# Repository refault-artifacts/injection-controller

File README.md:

# DDR5 Injection controller
Hardware design files and firmware for the injection controller PCB that
controls the DDR5 interposer PCB by using a Teensy 4.1 microcontroller. This is
a 2-layer PCB.

## Design
The schematic and PCB was designed in KiCAD. Open `hardware/injection-controller.kicad_pro` in KiCAD 8 or later to view the design files.
From there, you should be able to select the schematic and PCB layout.

For convenience, you can also find a PDF version of the schematic in `docs/schematic.pdf`. A bill of materials (BOM) is also provided in `docs`.

### !!! Important !!!
This injection controller was designed for a previous version
of interposer with a different pinout on the flat-flex connector.
This works fine as long as the software is modified accordingly,
but it means that the labels of J2 in the schematic of the injection
controller (e.g., `CA4_LOW`) are not accurate anymore.
Instead, match the pin number of J2 to the appropriate function
of the interposer that you use.
The latest fault injection interposer also requires 3.3 V instead
of 1.1V. Hence, the voltage regulator U2 should be replaced
with a 3.3V type.
To be able to power-cycle the experiment machine, we manually
added a mechanical relay with a driving transistor and flyback diode
to the PCB. Those components are not documented here.

## Features

  - **Ethernet**: RJ45 Jack connected to the Ethernet header pins of the Teensy.
 - **Pluggable Teensy**: The Teensy microcontroller board is meant to be
 attached to the PCB by using headers, allowing for easy replacement and
 swapping of microcontroller.
 - **Status LED**: One power LED and one user controllable LED on the board.
- **Flat flex connector**: By using a suitable flat flex cable, the controller
 can be easily connected to the DDR5 fault injector interposer.

## Manufacturing
The PCBs were manufactured by JLCPCB and were assembled by hand.
It is reasonable to also order a SMT stencil so soldering is easier.
The Gerber files needed for manufacturing are located at hardware/output.

### Manufactoring options
| Option  | Value   |
|---------|---------|
| Layers  |   2     |
| Dimension | 60.96 mm* 40 mm |
| Product Type | Industrial/Consumer electronics |
| Different Design | 1|
| Delivery Format | Single PCB|
| PCB Thickness | 1.6|
| Impedance Control | no|
| Layer Sequence ||
| PCB Color | Green|
| Silkscreen | White|
| Via Covering | Tented|
| Surface Finish | LeadFree HASL|
| Deburring/Edge rounding | No|
| Outer Copper Weight | 1|
| Gold Fingers | No|
| Flying Probe Test | Fully Test|
| Castellated Holes | no|
| Remove Order Number | No|
| 4-Wire Kelvin Test | No|
| Material Type | FR4-Standard TG 135-140|
| Paper between PCBs | No|
| Appearance Quality | IPC Class 2 Standard|
| Confirm Production file | No|
| Silkscreen Technology | Ink-jet/Screen Printing Silkscreen|
| Package Box | With JLCPCB logo |

## Assembly
Assembly can be done manually using a stencil (ordered with the PCB),
some solder paste and a hot air gun.
### Bill of Materials (BOM)
See docs/bom

## License
Some parts of the PCB may be subject to copyright of third parties 
(e.g. 3D models provided by manufacturer).
Otherwise, the design is released under MIT License.

The KiCad symbol and footprint libraries for the Teensy microcontroller 
are taken from [here](https://github.com/XenGi/teensy_library) 
and [here](https://github.com/XenGi/teensy.pretty), respectively (MIT License).

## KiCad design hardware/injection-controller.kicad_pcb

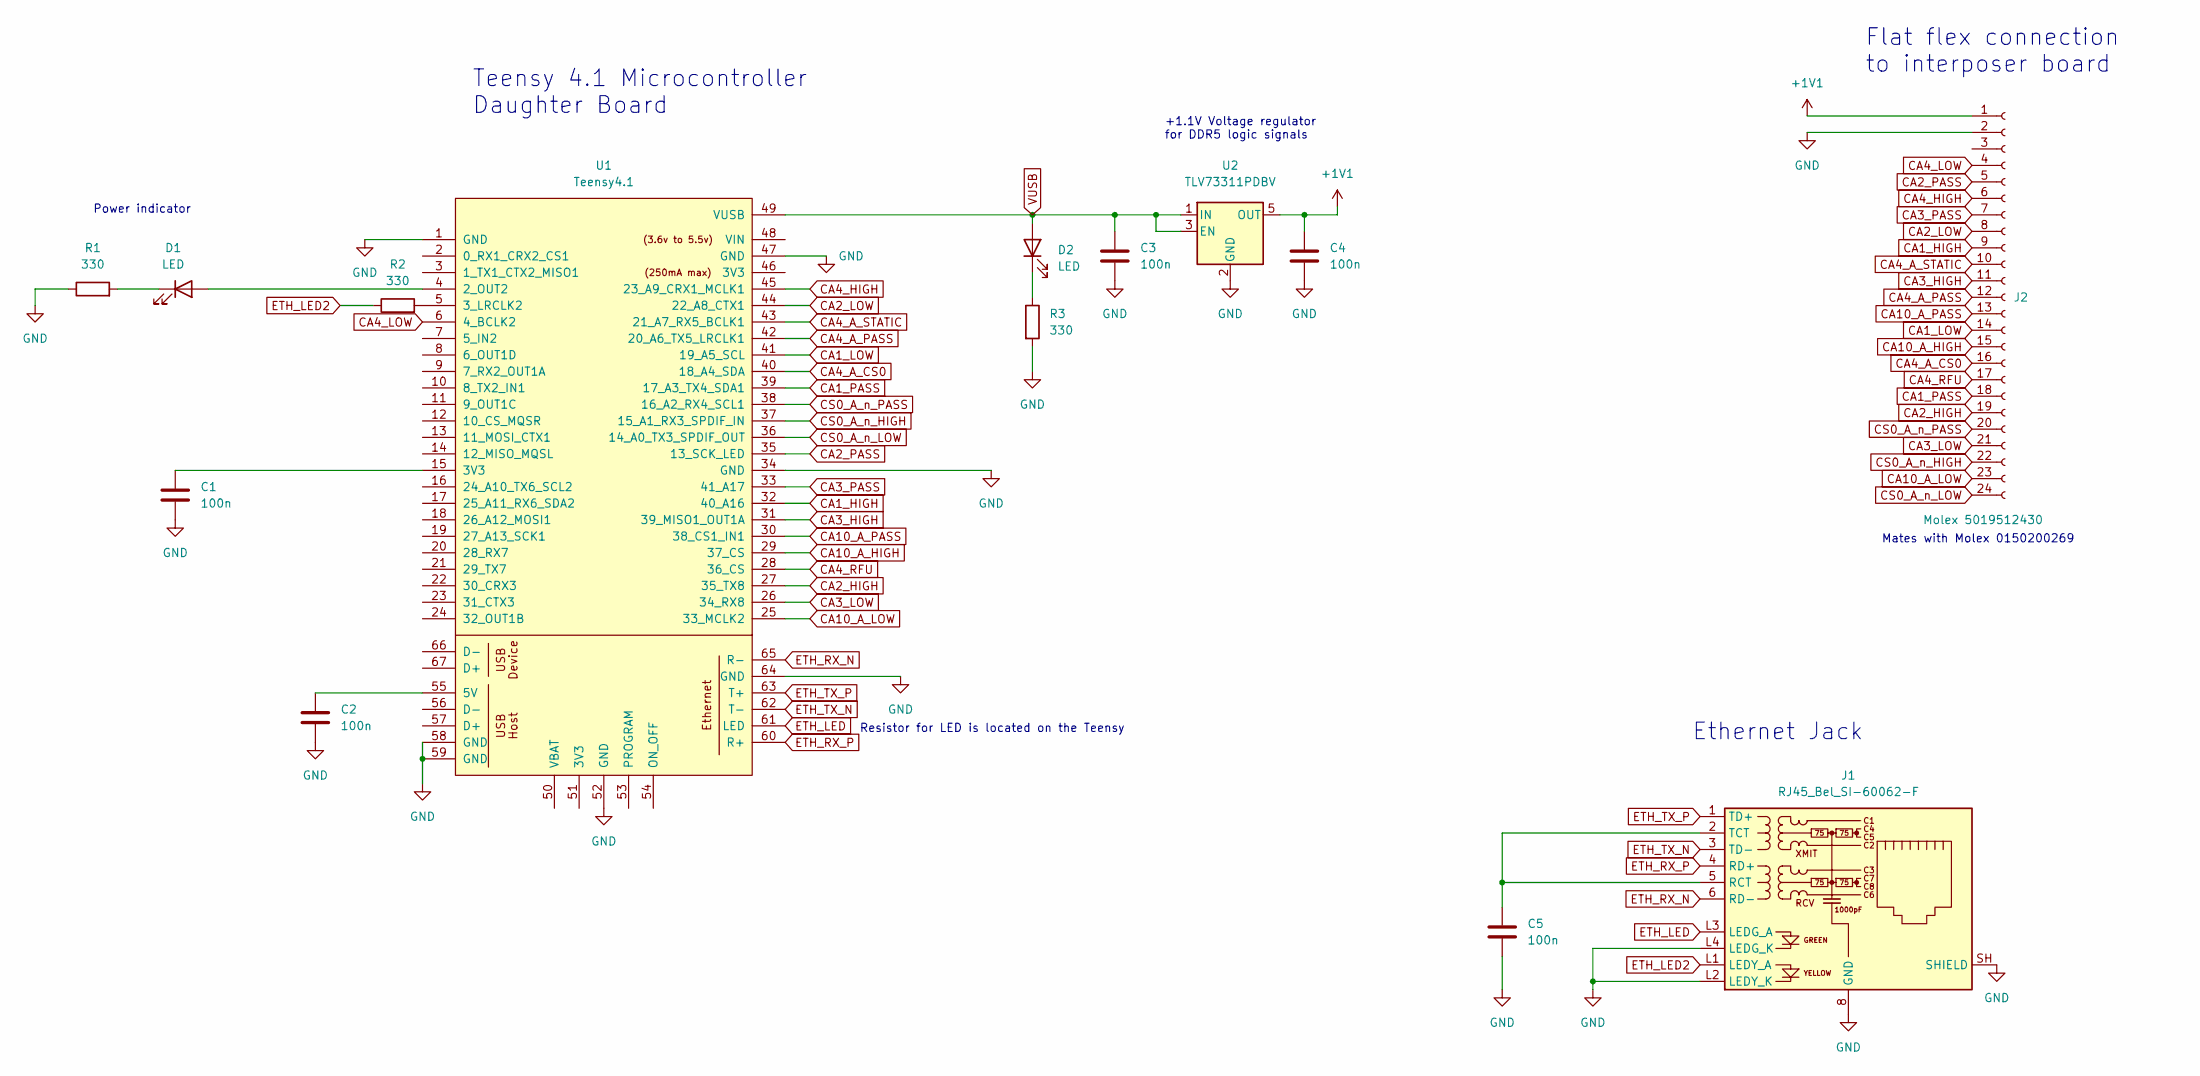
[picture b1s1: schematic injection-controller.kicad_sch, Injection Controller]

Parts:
C1, C2, C3, C4, C5: 100n; C_0603_1608Metric
D1, D2: LED; LED_0805_2012Metric
J1: RJ45_Bel_SI-60062-F; 480251090
J2: Molex 5019512430; 5019512430
R1, R2, R3: 330; R_0603_1608Metric
U1: Teensy4.1; Teensy41
U2: TLV73311PDBV; SOT-23-5

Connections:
+1V1: C4.1, J2.1, U2.5 (OUT)
CA1_HIGH: J2.9, U1.32 (40_A16)
CA1_LOW: J2.14, U1.41 (19_A5_SCL)
CA1_PASS: J2.18, U1.39 (17_A3_TX4_SDA1)
CA2_HIGH: J2.19, U1.27 (35_TX8)
CA2_LOW: J2.8, U1.44 (22_A8_CTX1)
CA2_PASS: J2.5, U1.35 (13_SCK_LED)
CA3_HIGH: J2.11, U1.31 (39_MISO1_OUT1A)
CA3_LOW: J2.21, U1.26 (34_RX8)
CA3_PASS: J2.7, U1.33 (41_A17)
CA4_A_CS0: J2.16, U1.40 (18_A4_SDA)
CA4_A_PASS: J2.12, U1.42 (20_A6_TX5_LRCLK1)
CA4_A_STATIC: J2.10, U1.43 (21_A7_RX5_BCLK1)
CA4_HIGH: J2.6, U1.45 (23_A9_CRX1_MCLK1)
CA4_LOW: J2.4, U1.6 (4_BCLK2)
CA4_RFU: J2.17, U1.28 (36_CS)
CA10_A_HIGH: J2.15, U1.29 (37_CS)
CA10_A_LOW: J2.23, U1.25 (33_MCLK2)
CA10_A_PASS: J2.13, U1.30 (38_CS1_IN1)
CS0_A_n_HIGH: J2.22, U1.37 (15_A1_RX3_SPDIF_IN)
CS0_A_n_LOW: J2.24, U1.36 (14_A0_TX3_SPDIF_OUT)
CS0_A_n_PASS: J2.20, U1.38 (16_A2_RX4_SCL1)
ETH_LED: J1.L3 (LEDG_A), U1.61 (LED)
ETH_LED2: J1.L1 (LEDY_A), R2.1
ETH_RX_N: J1.6 (RD-), U1.65 (R-)
ETH_RX_P: J1.4 (RD+), U1.60 (R+)
ETH_TX_N: J1.3 (TD-), U1.62 (T-)
ETH_TX_P: J1.1 (TD+), U1.63 (T+)
GND: C1.2, C2.2, C3.2, C4.2, C5.2, J1.8 (GND), J1.L2 (LEDY_K), J1.L4 (LEDG_K), J1.SH (SHIELD), J2.2, R1.1, R3.2, U1.1 (GND), U1.34 (GND), U1.47 (GND), U1.52 (GND), U1.58 (GND), U1.59 (GND), U1.64 (GND), U2.2 (GND)
unnamed: C1.1, U1.15 (3V3)
unnamed: C2.1, U1.55 (5V)
unnamed: C5.1, J1.2 (TCT), J1.5 (RCT)
unnamed: D1.1 (K), R1.2
unnamed: D1.2 (A), U1.4 (2_OUT2)
unnamed: D2.1 (K), R3.1
unnamed: R2.2, U1.5 (3_LRCLK2)
VUSB: C3.1, D2.2 (A), U1.49 (VUSB), U2.1 (IN), U2.3 (EN)

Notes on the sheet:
Mates with Molex 0150200269
+1.1V Voltage regulator for DDR5 logic signals
Flat flex connection to interposer board
Power indicator
Resistor for LED is located on the Teensy
Ethernet Jack
Teensy 4.1 Microcontroller Daughter Board

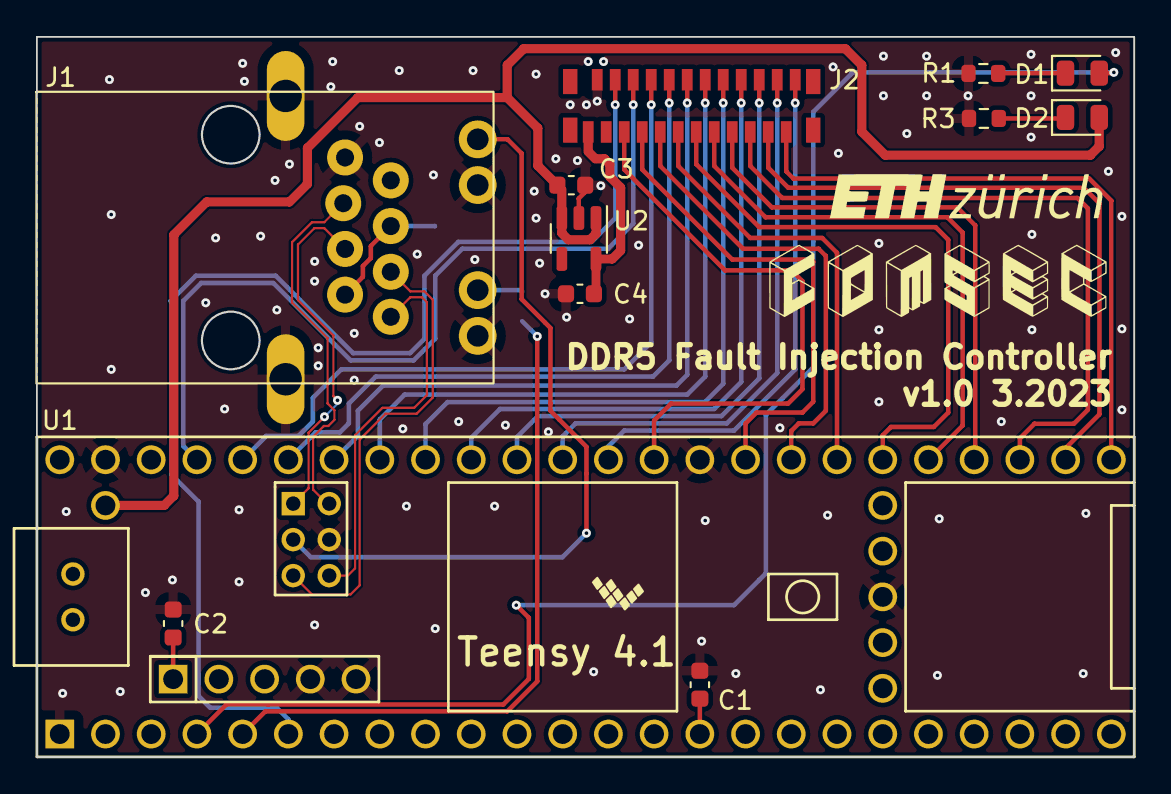
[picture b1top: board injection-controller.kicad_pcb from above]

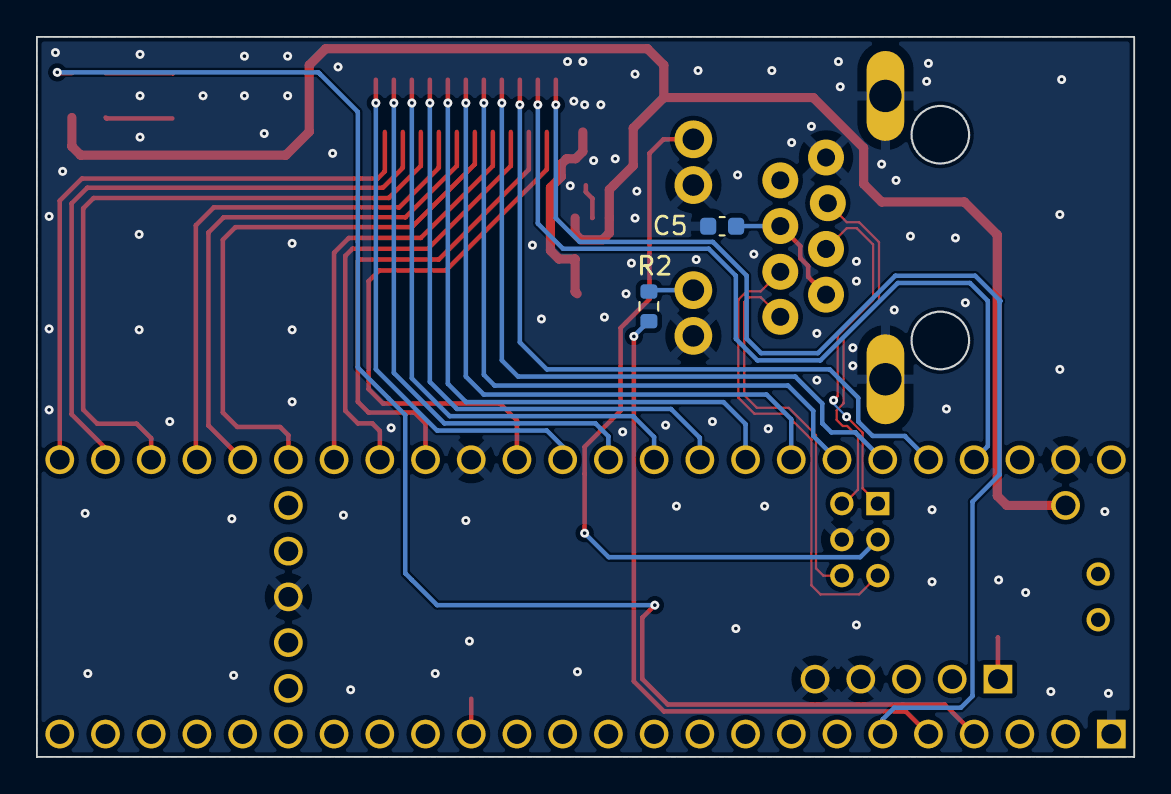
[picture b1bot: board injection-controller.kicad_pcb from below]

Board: 2 copper layers, 61.0 x 40.0 mm, 14 parts (2 on the bottom side), 37 nets.

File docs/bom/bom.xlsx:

Bill of Materials (BOM)
Project: | stgloor-injection-controller
Date: | 44992
No | Qty | Reference | Value | Footprint | Manufacturer | Manufacturer Part No. | Supplier | Supplier Part No. | Comment
1 | 1 | U1 |  | Teensy:Teensy41 | PJRC | TEENSY41 | PJRC | TEENSY41
2 | 1 | U2 |  | Package_TO_SOT_SMD:SOT-23-5 | Texas Instruments | TLV73311PQDBVRQ1 | Digikey | 296-TLV73311PQDBVRQ1TR-ND
3 | 2 | D1,D2 | Green | LED_SMD:LED_0805_2012Metric | Kingbright | APHCM2012CGCK-F01 | Digikey | 754-1094-2-ND
4 | 2 | R1,R2 | 120 | Resistor_SMD:R_0603_1608Metric | Bourns Inc. | CR0603-FX-1200ELF | Digikey | CR0603-FX-1200ELFTR-ND
5 | 1 | R3 | 330 | Resistor_SMD:R_0603_1608Metric | Bourns Inc. | CR0603-JW-331ELF | Digikey | CR0603-JW-331ELFTR-ND
6 | 5 | C1-C5 | 100n | Capacitor_SMD:C_0603_1608Metric | Samsung Electro-Mechanics | CL10B104KB8NNWC | Digikey | 1276-1935-2-ND
7 | 1 | J2 |  | ddr5:5019512430 | Molex | 501951-2430 | Mouser | 538-501951-2430
8 | 1 | J1 |  | DDR5:480251090 | Molex | 480251090 | Digikey | WM5483-ND

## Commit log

2025-02-08 feat: add files
2025-02-08 docs(readme): minor formatting change
2025-02-19 docs(readme): minor fixes
